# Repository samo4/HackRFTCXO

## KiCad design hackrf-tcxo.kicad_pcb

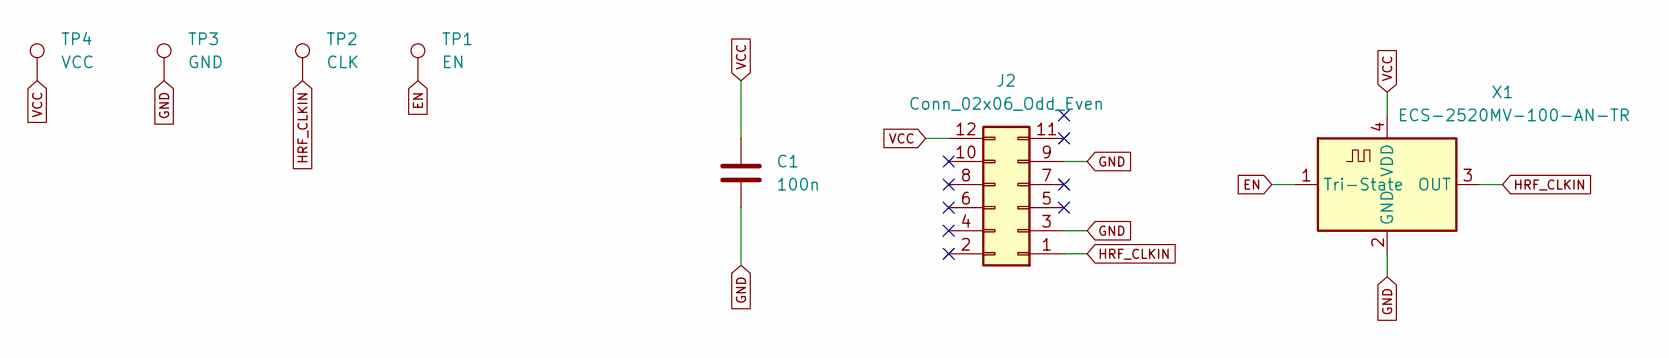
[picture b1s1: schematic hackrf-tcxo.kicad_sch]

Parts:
C1: 100n; C_0402_1005Metric
J2: Conn_02x06_Odd_Even; PinHeader_2x06_P2.54mm_Vertical_SMD
TP1: EN; TestPoint_Pad_D1.5mm
TP2: CLK; TestPoint_Pad_D1.5mm
TP3: GND; TestPoint_Pad_D1.5mm
TP4: VCC; TestPoint_Pad_D1.5mm
X1: ECS-2520MV-100-AN-TR; Oscillator_SMD_ECS_2520MV-xxx-xx-4Pin_2.5x2.0mm

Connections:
EN: TP1.1, X1.1 (Tri-State)
GND: C1.2, J2.3, J2.9, TP3.1, X1.2 (GND)
HRF_CLKIN: J2.1, TP2.1, X1.3 (OUT)
VCC: C1.1, J2.12, TP4.1, X1.4 (VDD)

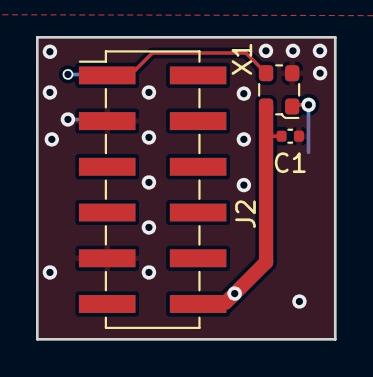
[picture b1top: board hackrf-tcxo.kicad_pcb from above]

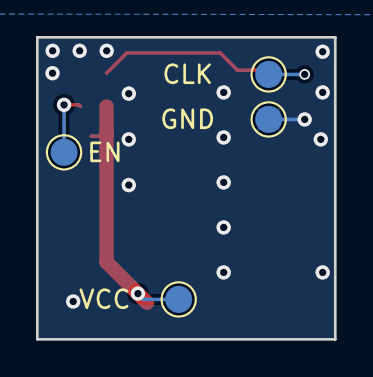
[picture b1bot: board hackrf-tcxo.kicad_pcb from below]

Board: 2 copper layers, 16.6 x 16.8 mm, 7 parts (4 on the bottom side), 4 nets.

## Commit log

2024-08-01 smth
